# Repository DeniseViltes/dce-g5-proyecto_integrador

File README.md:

# Proyecto de diseño: Sistema de alimentación para aplicaciones industriales y automotrices
>[!TIP]
>holaa
## Grupo 5

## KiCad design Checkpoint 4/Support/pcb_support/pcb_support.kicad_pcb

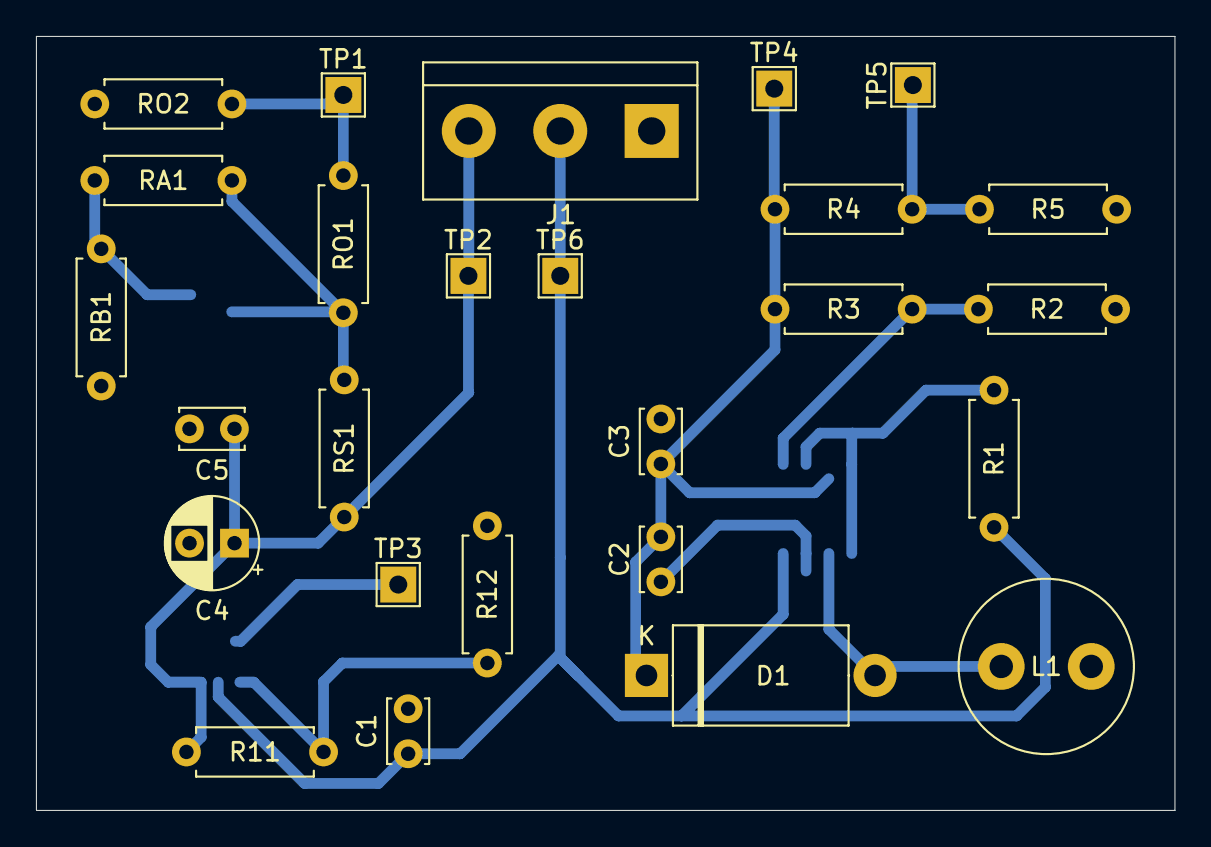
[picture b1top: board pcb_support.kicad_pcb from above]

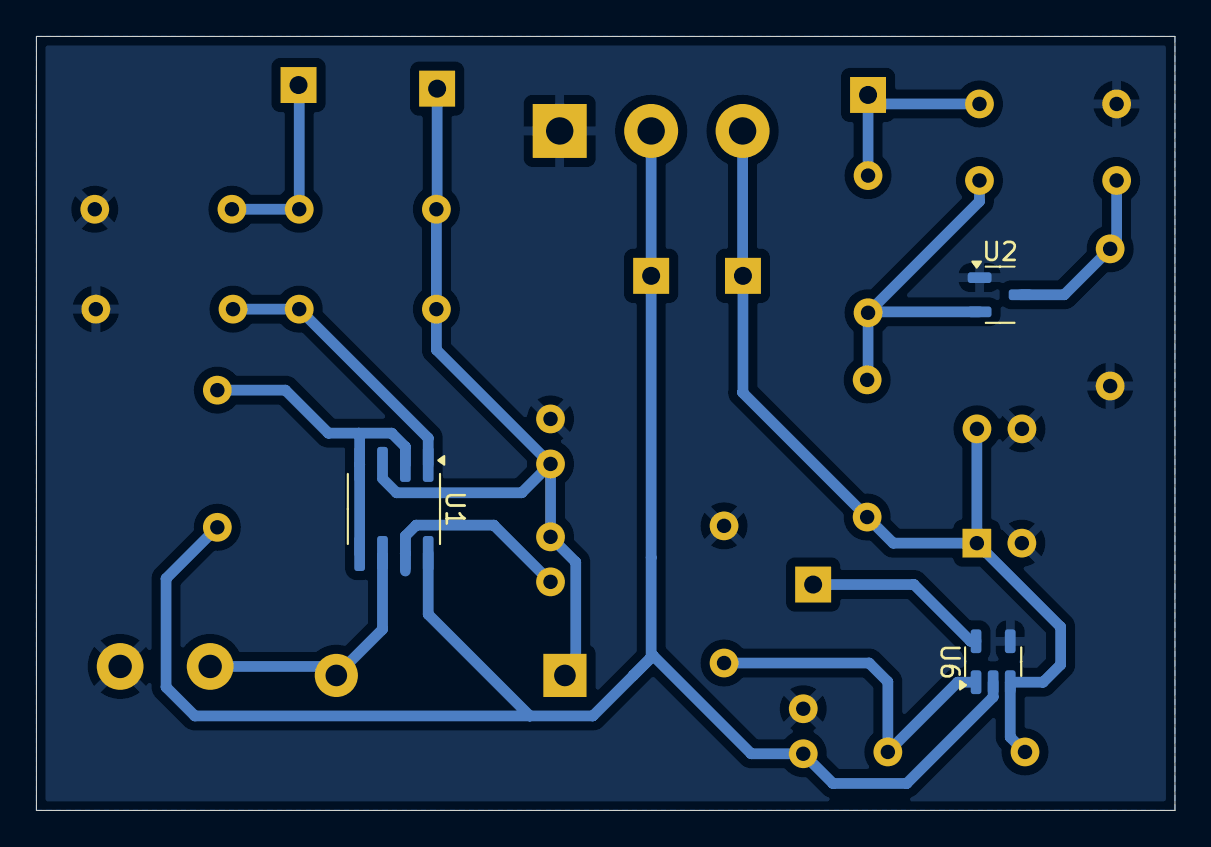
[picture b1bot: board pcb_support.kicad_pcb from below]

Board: 2 copper layers, 63.2 x 43.0 mm, 29 parts (3 on the bottom side), 14 nets.

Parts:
C1, C3: 100µ; C_Disc_D3.4mm_W2.1mm_P2.50mm
C2: 1.5n; C_Disc_D3.4mm_W2.1mm_P2.50mm
C4: 10µ; CP_Radial_D5.0mm_P2.50mm
C5: 100n; C_Disc_D3.4mm_W2.1mm_P2.50mm
D1: RBQ20T45ANZ; D_DO-27_P12.70mm_Horizontal
J1: Conn_01x03_Socket; TerminalBlock_bornier-3_P5.08mm
L1: 90µ; L_Radial_D9.5mm_P5.00mm_Fastron_07HVP
R1: 0.22; R_Axial_DIN0207_L6.3mm_D2.5mm_P7.62mm_Horizontal
R2: 8.2k; R_Axial_DIN0207_L6.3mm_D2.5mm_P7.62mm_Horizontal
R3: 953; R_Axial_DIN0207_L6.3mm_D2.5mm_P7.62mm_Horizontal
R4: 1k; R_Axial_DIN0207_L6.3mm_D2.5mm_P7.62mm_Horizontal
R5: 1.1k; R_Axial_DIN0207_L6.3mm_D2.5mm_P7.62mm_Horizontal
R11: 10k; R_Axial_DIN0207_L6.3mm_D2.5mm_P7.62mm_Horizontal
R12: 11.24k; R_Axial_DIN0207_L6.3mm_D2.5mm_P7.62mm_Horizontal
RA1: 10; R_Axial_DIN0207_L6.3mm_D2.5mm_P7.62mm_Horizontal
RB1: 100k; R_Axial_DIN0207_L6.3mm_D2.5mm_P7.62mm_Horizontal
RO1: 1.5k; R_Axial_DIN0207_L6.3mm_D2.5mm_P7.62mm_Horizontal
RO2: 1.4k; R_Axial_DIN0207_L6.3mm_D2.5mm_P7.62mm_Horizontal
RS1: 1k; R_Axial_DIN0207_L6.3mm_D2.5mm_P7.62mm_Horizontal
TP1, TP2, TP3, TP4, TP5, TP6: TestPoint; TestPoint_THTPad_2.0x2.0mm_Drill1.0mm
U1: MC33063A-Q1_TRANS; SOIC-8_3.9x4.9mm_P1.27mm
U2: TL431; SOT-23-3
U6: TLV3201; SOT-23-5

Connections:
0: C1.2, C3.2, C4.2, C5.2, J1.1, L1.2, R2.2, R5.1, R12.1, RB1.2, RO2.2, U2.1 (2), U6.4 (GND)
-VPOSA: R4.1, R5.2, TP5.1
-Vbat: C2.2, C3.1, D1.1 (+), R3.1, R4.2, TP4.1, U1.3 (GND)
unnamed: D1.2 (-), L1.1, U1.6 (SE)
unnamed: R2.1, R3.2, U1.1 (CII)
unnamed: R1.1, U1.2 (DC), U1.4 (Ipk), U1.5 (SC)
unnamed: C2.1, U1.7 (TC)
unnamed: RA1.2, RB1.1, U2.3 (1)
unnamed: RA1.1, RO1.1, RS1.2, U2.2 (3)
unnamed: R11.1, R12.2, U6.1 (IN+)
Vbat: C4.1, C5.1, J1.3, R11.2, RS1.1, TP2.1, U6.3 (Vcc)
Vbuck: C1.1, J1.2, R1.2, TP6.1, U1.8 (VCC), U6.2 (IN-)
Venable: TP3.1, U6.5 (OUT)
Vref: RO1.2, RO2.1, TP1.1

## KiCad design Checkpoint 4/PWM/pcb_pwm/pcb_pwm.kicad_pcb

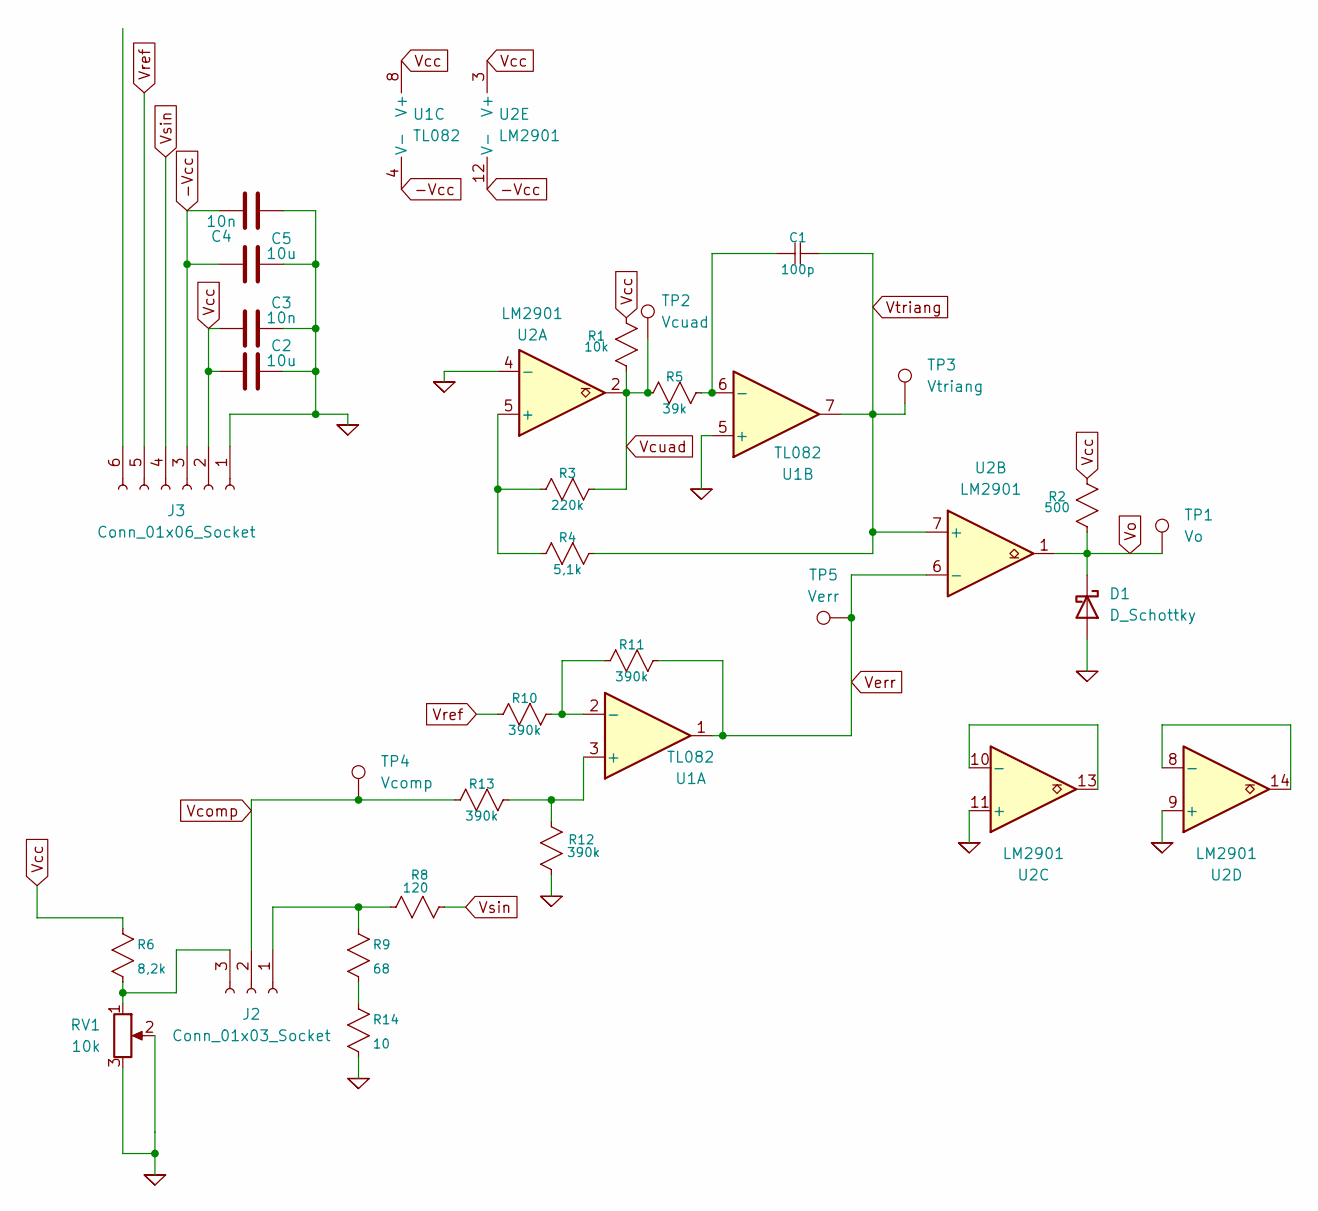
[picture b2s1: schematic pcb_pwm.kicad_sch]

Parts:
C1: 100p; C_Disc_D3.4mm_W2.1mm_P2.50mm
C2, C5: 10u; CP_Radial_D5.0mm_P2.50mm
C3, C4: 10n; C_Disc_D4.3mm_W1.9mm_P5.00mm
D1: D_Schottky; TO-220-2_Vertical
J2: Conn_01x03_Socket; PinHeader_1x03_P2.54mm_Vertical
J3: Conn_01x06_Socket; TerminalBlock_bornier-6_P5.08mm
R1: 10k; R_Axial_DIN0207_L6.3mm_D2.5mm_P7.62mm_Horizontal
R2: 500; R_Axial_DIN0207_L6.3mm_D2.5mm_P7.62mm_Horizontal
R3: 220k; R_Axial_DIN0207_L6.3mm_D2.5mm_P7.62mm_Horizontal
R4: 5,1k; R_Axial_DIN0207_L6.3mm_D2.5mm_P7.62mm_Horizontal
R5: 39k; R_Axial_DIN0207_L6.3mm_D2.5mm_P7.62mm_Horizontal
R6: 8,2k; R_Axial_DIN0207_L6.3mm_D2.5mm_P7.62mm_Horizontal
R8: 120; R_Axial_DIN0207_L6.3mm_D2.5mm_P7.62mm_Horizontal
R9: 68; R_Axial_DIN0207_L6.3mm_D2.5mm_P7.62mm_Horizontal
R10, R11, R12, R13: 390k; R_Axial_DIN0207_L6.3mm_D2.5mm_P7.62mm_Horizontal
R14: 10; R_Axial_DIN0207_L6.3mm_D2.5mm_P7.62mm_Horizontal
RV1: 10k; Potentiometer_Piher_PC-16_Single_Horizontal
TP1: Vo; TestPoint_THTPad_1.3x1.3mm_Drill0.7mm
TP2: Vcuad; TestPoint_THTPad_1.3x1.3mm_Drill0.7mm
TP3: Vtriang; TestPoint_THTPad_1.3x1.3mm_Drill0.7mm
TP4: Vcomp; TestPoint_THTPad_1.3x1.3mm_Drill0.7mm
TP5: Verr; TestPoint_THTPad_1.3x1.3mm_Drill0.7mm
U1: TL082; DIP-8_W7.62mm_Socket
U2: LM2901; DIP-14_W7.62mm_Socket

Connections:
0: C2.2, C3.2, C4.1, C5.2, D1.2 (A), J3.1, R12.2, R14.2, RV1.2, RV1.3, U1.5 (+), U2.4 (-), U2.9 (+), U2.11 (+)
-Vcc: C4.2, C5.1, J3.3, U1.4 (V-), U2.12 (V-)
unnamed: J2.1, R8.1, R9.1
unnamed: J2.3, R6.2, RV1.1
unnamed: R9.2, R14.1
unnamed: R12.1, R13.1, U1.3 (+)
unnamed: R10.1, R11.2, U1.2 (-)
unnamed: C1.2, R5.1, U1.6 (-)
unnamed: R3.2, R4.2, U2.5 (+)
unnamed: U2.10 (-), U2.13
unnamed: U2.8 (-), U2.14
Vcc: C2.1, C3.1, J3.2, R1.2, R2.2, R6.1, U1.8 (V+), U2.3 (V+)
Vcomp: J2.2, R13.2, TP4.1
Vcuad: R1.1, R3.1, R5.2, TP2.1, U2.2
Verr: R11.1, TP5.1, U1.1, U2.6 (-)
Vo: D1.1 (K), R2.1, TP1.1, U2.1
Vref: J3.5, R10.2
Vsin: J3.4, R8.2
Vtriang: C1.1, R4.1, TP3.1, U1.7, U2.7 (+)

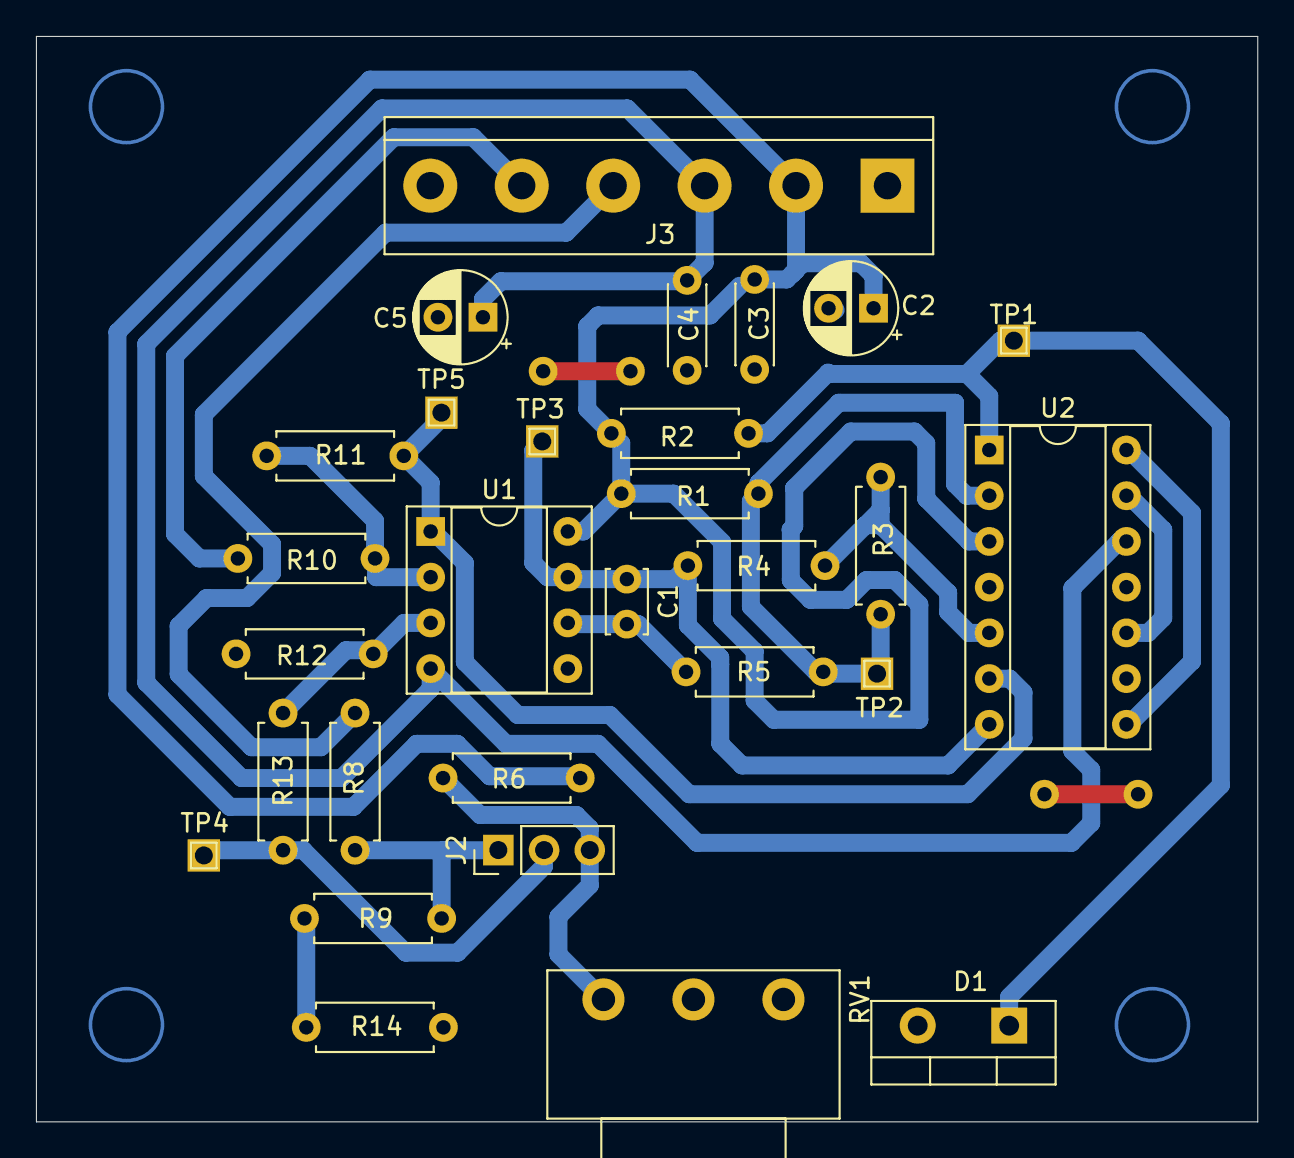
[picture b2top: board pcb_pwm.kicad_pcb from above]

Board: 2 copper layers, 67.8 x 60.3 mm, 29 parts (0 on the bottom side), 19 nets.

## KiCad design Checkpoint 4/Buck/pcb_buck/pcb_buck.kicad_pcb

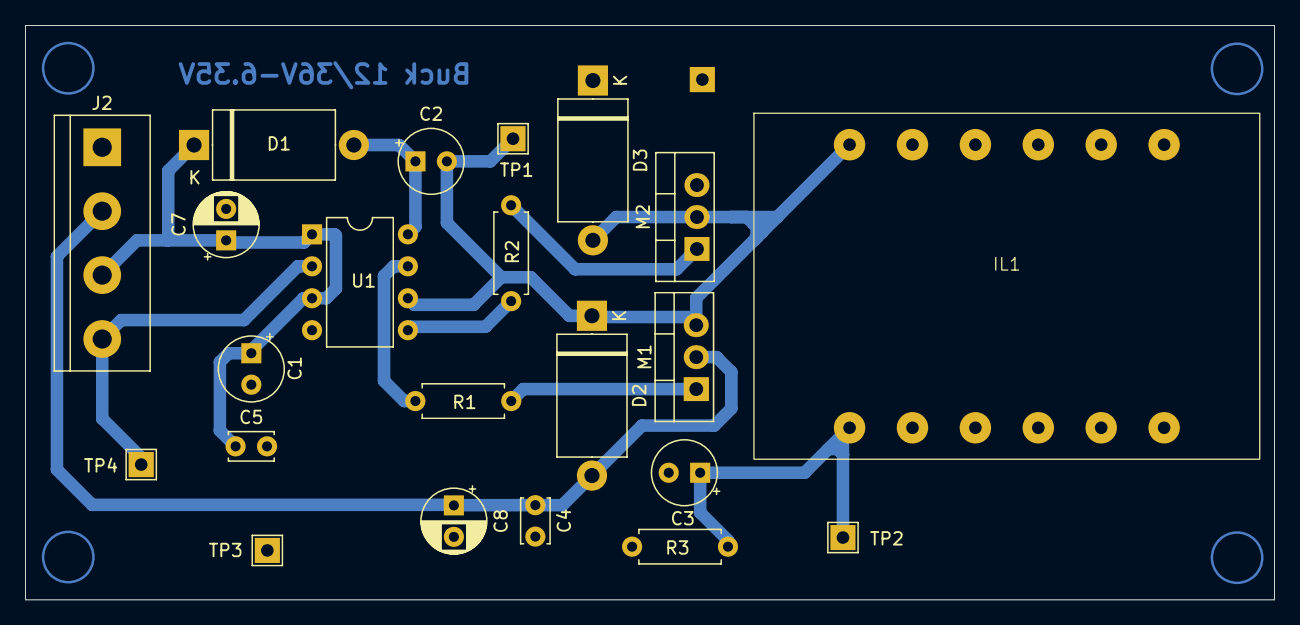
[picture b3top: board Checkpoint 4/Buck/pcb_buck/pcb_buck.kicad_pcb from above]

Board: 2 copper layers, 99.3 x 45.6 mm, 22 parts (0 on the bottom side), 11 nets.

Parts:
C1: 1µ; CP_Radial_Tantal_D5.0mm_P2.50mm
C2: 330n; CP_Radial_Tantal_D5.0mm_P2.50mm
C3: 150n; CP_Radial_Tantal_D5.0mm_P2.50mm
C4, C5: 100n; C_Disc_D3.4mm_W2.1mm_P2.50mm
C7, C8: 10u; CP_Radial_D5.0mm_P2.50mm
D1, D2, D3: D1n5822rl; D_DO-27_P12.70mm_Horizontal
IL1: 700µ; Inductor
J2: Conn_01x04_Socket; TerminalBlock_bornier-4_P5.08mm
M1, M2: IRLZ44N; TO-220-3_Vertical
R1, R2: 10; R_Axial_DIN0207_L6.3mm_D2.5mm_P7.62mm_Horizontal
R3: 390; R_Axial_DIN0207_L6.3mm_D2.5mm_P7.62mm_Horizontal
TP1: Vd; TestPoint_THTPad_2.0x2.0mm_Drill1.0mm
TP2: Vo; TestPoint_THTPad_2.0x2.0mm_Drill1.0mm
TP3: GND; TestPoint_THTPad_2.0x2.0mm_Drill1.0mm
TP4: PWM; TestPoint_THTPad_2.0x2.0mm_Drill1.0mm
U1: IR2104; DIP-8_W7.62mm

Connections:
0: C1.2, C3.2, C4.2, C5.2, C7.2, C8.2, D3.1 (+), J2.1, M2.3 (S), R3.2, TP3.1, U1.4 (COM)
unnamed: C2.1, D1.2 (-), U1.8 (LO)
unnamed: M1.1 (D), R1.1
unnamed: M2.1 (D), R2.1
unnamed: R1.2, U1.7 (VS)
unnamed: R2.2, U1.5 (VB)
Vd: C2.2, D2.1 (+), D3.2 (-), IL1.7, M1.3 (S), M2.2 (G), TP1.1, U1.6 (HO)
Vo: C3.1, IL1.1, R3.1, TP2.1
pwm: J2.4, TP4.1, U1.2 (IN)
vcc: C1.1, C5.1, C7.1, D1.1 (+), J2.3, U1.1 (VCC), U1.3 (NSD)
vdd: C4.1, C8.1, D2.2 (-), J2.2, M1.2 (G)

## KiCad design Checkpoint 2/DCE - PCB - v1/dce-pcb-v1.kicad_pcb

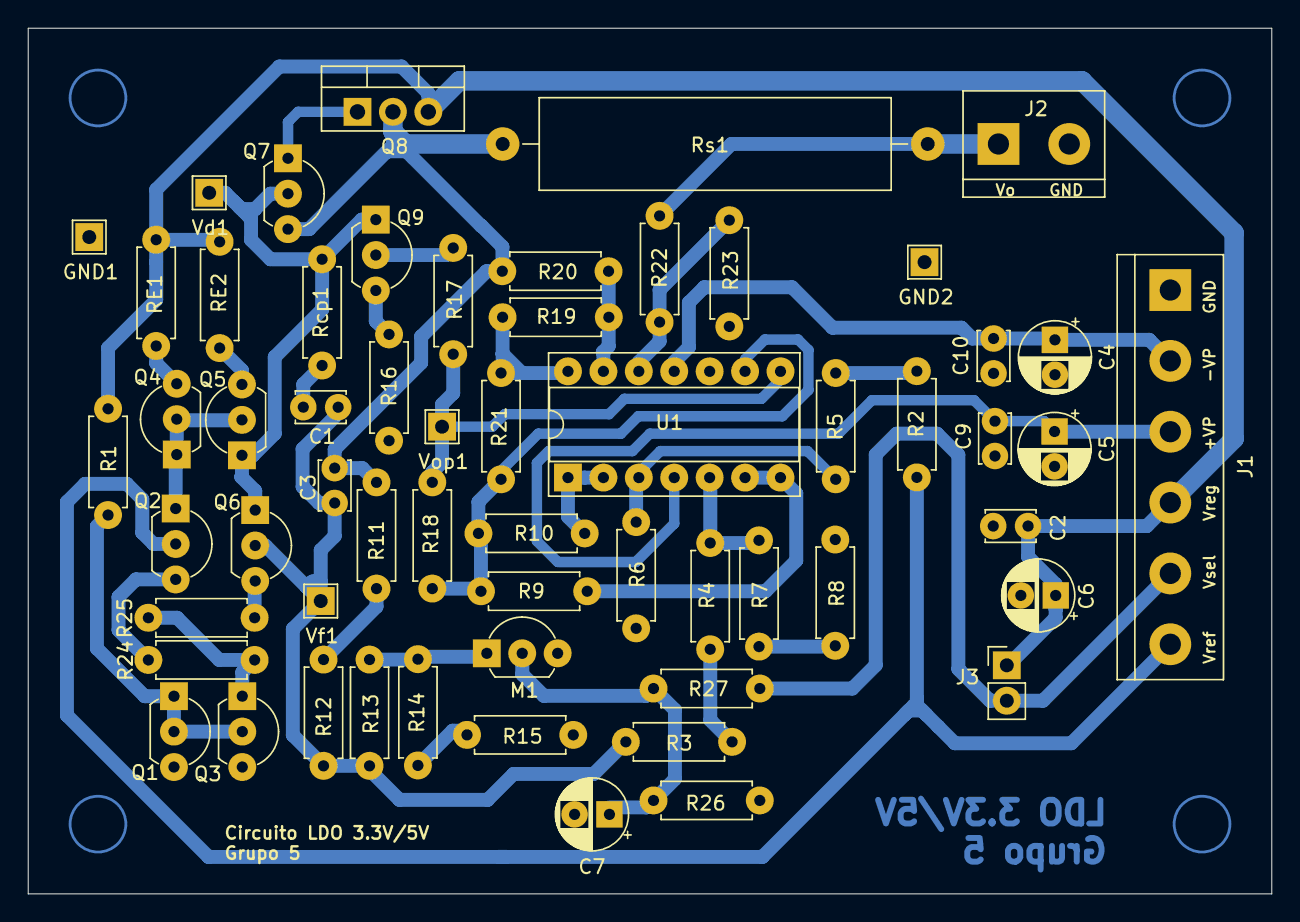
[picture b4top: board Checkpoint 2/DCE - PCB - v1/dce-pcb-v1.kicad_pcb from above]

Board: 2 copper layers, 89.2 x 62.1 mm, 59 parts (0 on the bottom side), 37 nets.

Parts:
C1: 2.2n; C_Disc_D3.4mm_W2.1mm_P2.50mm
C2, C9, C10: 10n; C_Disc_D3.4mm_W2.1mm_P2.50mm
C3: 100p; C_Disc_D3.4mm_W2.1mm_P2.50mm
C4, C5, C6: 10u; CP_Radial_D5.0mm_P2.50mm
C7: C; CP_Radial_D5.0mm_P2.50mm
GND1, GND2: TestPoint; TestPoint_THTPad_2.0x2.0mm_Drill1.0mm
J1: Conn_01x06_Socket; TerminalBlock_bornier-6_P5.08mm
J2: Conn_01x02_Socket; TerminalBlock_bornier-2_P5.08mm
J3: Conn_01x02_Socket; PinHeader_1x02_P2.54mm_Vertical
M1: 2N7000; TO-92L_Inline_Wide
Q1, Q2, Q3, Q6, Q9: BC547B; TO-92L_Inline_Wide
Q4, Q5: BC557B; TO-92L_Inline_Wide
Q7: TIP41C; TO-92L_Inline_Wide
Q8: TIP42C; TO-220-3_Vertical
R1: 3.3k; R_Axial_DIN0207_L6.3mm_D2.5mm_P7.62mm_Horizontal
R2: 5.6k; R_Axial_DIN0207_L6.3mm_D2.5mm_P7.62mm_Horizontal
R3, R7: 6.8k; R_Axial_DIN0207_L6.3mm_D2.5mm_P7.62mm_Horizontal
R4: 1.2k; R_Axial_DIN0207_L6.3mm_D2.5mm_P7.62mm_Horizontal
R5, R11: 2.7k; R_Axial_DIN0207_L6.3mm_D2.5mm_P7.62mm_Horizontal
R6, R9, R10, R21: 1.5k; R_Axial_DIN0207_L6.3mm_D2.5mm_P7.62mm_Horizontal
R8: 510; R_Axial_DIN0207_L6.3mm_D2.5mm_P7.62mm_Horizontal
R12: 390; R_Axial_DIN0207_L6.3mm_D2.5mm_P7.62mm_Horizontal
R13: 1K; R_Axial_DIN0207_L6.3mm_D2.5mm_P7.62mm_Horizontal
R14: 680; R_Axial_DIN0207_L6.3mm_D2.5mm_P7.62mm_Horizontal
R15: 270; R_Axial_DIN0207_L6.3mm_D2.5mm_P7.62mm_Horizontal
R16: 100; R_Axial_DIN0207_L6.3mm_D2.5mm_P7.62mm_Horizontal
R17, R20, R22, R26, R27: 1k; R_Axial_DIN0207_L6.3mm_D2.5mm_P7.62mm_Horizontal
R18: 100k; R_Axial_DIN0207_L6.3mm_D2.5mm_P7.62mm_Horizontal
R19, R23: 10k; R_Axial_DIN0207_L6.3mm_D2.5mm_P7.62mm_Horizontal
R24, R25: 10; R_Axial_DIN0207_L6.3mm_D2.5mm_P7.62mm_Horizontal
RE1, RE2: 470; R_Axial_DIN0207_L6.3mm_D2.5mm_P7.62mm_Horizontal
Rcp1: 220; R_Axial_DIN0207_L6.3mm_D2.5mm_P7.62mm_Horizontal
Rs1: 0.1; R_Axial_Power_L25.0mm_W6.4mm_P30.48mm
U1: LM324; DIP-14_W7.62mm_Socket
Vd1: TestPoint; TestPoint_THTPad_2.0x2.0mm_Drill1.0mm
Vf1: TestPoint; TestPoint_THTPad_2.0x2.0mm_Drill1.0mm
Vop1: TestPoint; TestPoint_THTPad_2.0x2.0mm_Drill1.0mm

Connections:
0: C2.2, C4.2, C5.2, C6.2, C7.2, C9.2, C10.2, GND1.1, GND2.1, J1.1, J2.2, M1.3 (S), Q1.3 (E), Q3.3 (E), R6.2, R8.2, R15.2, R16.2, R23.2, R26.2, U1.10 (+)
/+VPOSA: C5.1, C9.1, J1.3, U1.4 (V+)
/-VPOSA: C4.1, C10.1, J1.2, U1.11 (V-)
/Sum: R9.1, R10.1, R18.1, R21.2, U1.9 (-)
/Vf: C1.2, C3.2, Q6.2 (B), R3.2, R12.2, R13.1, Vf1.1
/Vlc: Q5.1 (C), Q6.1 (C), Q7.2 (B), Q9.1 (C), Rcp1.1, Vd1.1
/Vo: J2.1, R22.1, Rs1.1
/Vref: J1.6, Q2.2 (B), R2.2
/Vreg: C2.1, C6.1, J1.4, J3.1, Q8.3 (E), R1.1, RE1.1, RE2.1
/Vsel: J1.5, J3.2, R27.2
unnamed: C1.1, Rcp1.2
unnamed: M1.1 (D), R13.2, R14.1
unnamed: C7.1, M1.2 (G), R26.1, R27.1
unnamed: Q1.1 (C), Q1.2 (B), Q3.2 (B), R1.2
unnamed: Q2.1 (C), Q4.1 (C), Q4.2 (B), Q5.2 (B)
unnamed: Q2.3 (E), R24.1
unnamed: Q3.1 (C), R24.2, R25.1
unnamed: Q4.3 (E), RE1.2
unnamed: Q5.3 (E), RE2.2
unnamed: Q6.3 (E), R25.2
unnamed: Q7.1 (C), Q8.1 (C)
unnamed: C3.1, Q7.3 (E), Q8.2 (B), R11.1, R20.1, Rs1.2
unnamed: Q9.2 (B), R17.2
unnamed: Q9.3 (E), R16.1
unnamed: R2.1, R5.2
unnamed: R3.1, R4.2
unnamed: R7.2, R8.1
unnamed: R11.2, R12.1
unnamed: R14.2, R15.1
unnamed: R17.1, R18.2, U1.8, Vop1.1
unnamed: R19.2, R21.1, U1.14
unnamed: R5.1, R6.1, U1.3 (+)
unnamed: R10.2, U1.1, U1.2 (-)
unnamed: R4.1, R7.1, U1.5 (+)
unnamed: R9.2, U1.6 (-), U1.7
unnamed: R22.2, R23.1, U1.12 (+)
unnamed: R19.1, R20.2, U1.13 (-)

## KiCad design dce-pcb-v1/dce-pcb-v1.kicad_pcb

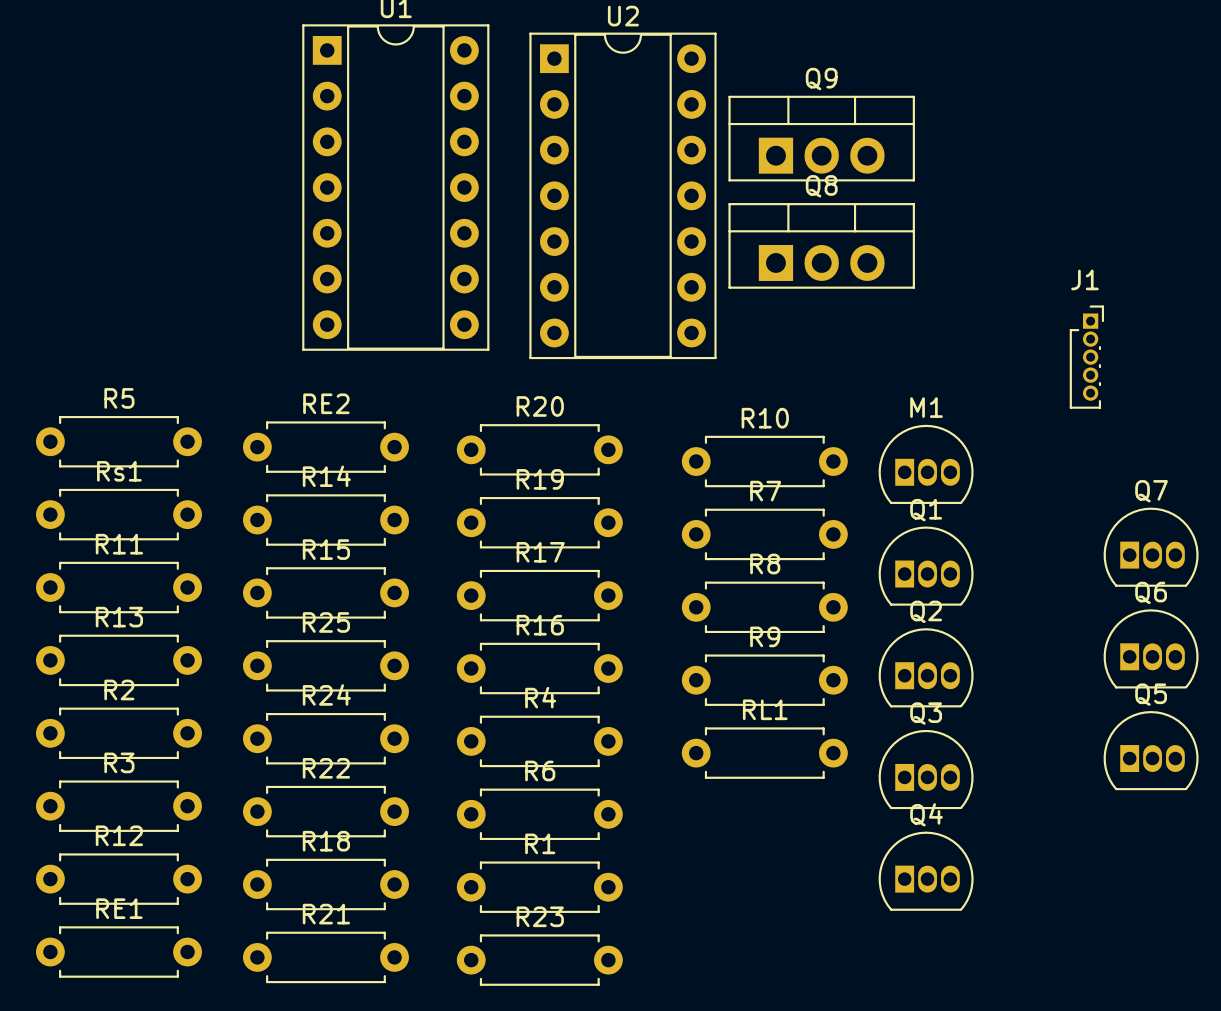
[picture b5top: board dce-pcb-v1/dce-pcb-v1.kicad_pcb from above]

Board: 2 copper layers, 42 parts (0 on the bottom side), 37 nets, no tracks yet.

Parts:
J1: Conn_01x05_Socket; PinSocket_1x05_P1.00mm_Vertical
M1: 2N7000; TO-92L_Inline
Q1, Q2: BC557B; TO-92L_Inline
Q3, Q4, Q5, Q6, Q7: BC547B; TO-92L_Inline
Q8: TIP41C; TO-220-3_Vertical
Q9: TIP42C; TO-220-3_Vertical
R1, R23: 2.7k; R_Axial_DIN0207_L6.3mm_D2.5mm_P7.62mm_Horizontal
R2: 390; R_Axial_DIN0207_L6.3mm_D2.5mm_P7.62mm_Horizontal
R3: 1K; R_Axial_DIN0207_L6.3mm_D2.5mm_P7.62mm_Horizontal
R4: 680; R_Axial_DIN0207_L6.3mm_D2.5mm_P7.62mm_Horizontal
R5: 270; R_Axial_DIN0207_L6.3mm_D2.5mm_P7.62mm_Horizontal
R6: 3.3k; R_Axial_DIN0207_L6.3mm_D2.5mm_P7.62mm_Horizontal
R7, R8, R11, R13, R15: 1k; R_Axial_DIN0207_L6.3mm_D2.5mm_P7.62mm_Horizontal
R9, R10: 10k; R_Axial_DIN0207_L6.3mm_D2.5mm_P7.62mm_Horizontal
R12, R14: 100k; R_Axial_DIN0207_L6.3mm_D2.5mm_P7.62mm_Horizontal
R16, R17, R18, R19, R22: 1.5k; R_Axial_DIN0207_L6.3mm_D2.5mm_P7.62mm_Horizontal
R20: 6.8k; R_Axial_DIN0207_L6.3mm_D2.5mm_P7.62mm_Horizontal
R21: 8.2k; R_Axial_DIN0207_L6.3mm_D2.5mm_P7.62mm_Horizontal
R24: 4.7k; R_Axial_DIN0207_L6.3mm_D2.5mm_P7.62mm_Horizontal
R25: 100; R_Axial_DIN0207_L6.3mm_D2.5mm_P7.62mm_Horizontal
RE1, RE2: 470; R_Axial_DIN0207_L6.3mm_D2.5mm_P7.62mm_Horizontal
RL1: RL; R_Axial_DIN0207_L6.3mm_D2.5mm_P7.62mm_Horizontal
Rs1: 0.1; R_Axial_DIN0207_L6.3mm_D2.5mm_P7.62mm_Horizontal
U1, U2: LM324; DIP-14_W7.62mm_Socket

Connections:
0: J1.1, M1.3 (S), Q5.3 (E), Q6.3 (E), R5.2, R9.2, R12.2, R17.2, R20.2, R22.2, R25.2, RL1.2, U1.11 (V-), U2.11 (V-)
/VPOSA: J1.2, U1.4 (V+), U2.4 (V+)
/Vf: Q4.2 (B), R2.2, R3.1, R21.2
/Vlc: Q2.1 (C), Q4.1 (C), Q7.1 (C), Q8.2 (B)
/Vo: R8.1, RL1.1, Rs1.1
/Vref: J1.3, Q3.2 (B), R24.2
/Vreg: J1.4, Q9.3 (E), R6.1, RE1.1, RE2.1
/Vsel: J1.5, M1.2 (G)
/vref-c: R13.1, R16.1, U1.8
unnamed: M1.1 (D), R3.2, R4.1
unnamed: Q1.1 (C), Q1.2 (B), Q2.2 (B), Q3.1 (C)
unnamed: Q1.3 (E), RE1.2
unnamed: Q2.3 (E), RE2.2
unnamed: Q3.3 (E), Q4.3 (E), Q6.1 (C)
unnamed: Q5.1 (C), Q5.2 (B), Q6.2 (B), R6.2
unnamed: Q7.2 (B), R15.2
unnamed: Q7.3 (E), R25.1
unnamed: Q8.1 (C), Q9.2 (B)
unnamed: Q8.3 (E), Q9.1 (C), R1.1, R7.1, Rs1.2
unnamed: R1.2, R2.1
unnamed: R4.2, R5.1
unnamed: R10.2, R11.1, U2.1
unnamed: R14.2, R15.1, U2.7
unnamed: R23.2, R24.1
unnamed: R22.1, R23.1, U1.3 (+)
unnamed: R18.2, U1.1, U1.2 (-)
unnamed: R20.1, R21.1, U1.5 (+)
unnamed: R19.2, U1.6 (-), U1.7
unnamed: R18.1, R19.1, U1.10 (+)
unnamed: R16.2, R17.1, U1.9 (-)
unnamed: U1.12 (+), U1.13 (-), U1.14
unnamed: R7.2, R9.1, U2.3 (+)
unnamed: R8.2, R10.1, U2.2 (-)
unnamed: R11.2, R12.1, U2.5 (+)
unnamed: R13.2, R14.1, U2.6 (-)
unnamed: U2.8, U2.9 (-), U2.10 (+)
unnamed: U2.12 (+), U2.13 (-), U2.14

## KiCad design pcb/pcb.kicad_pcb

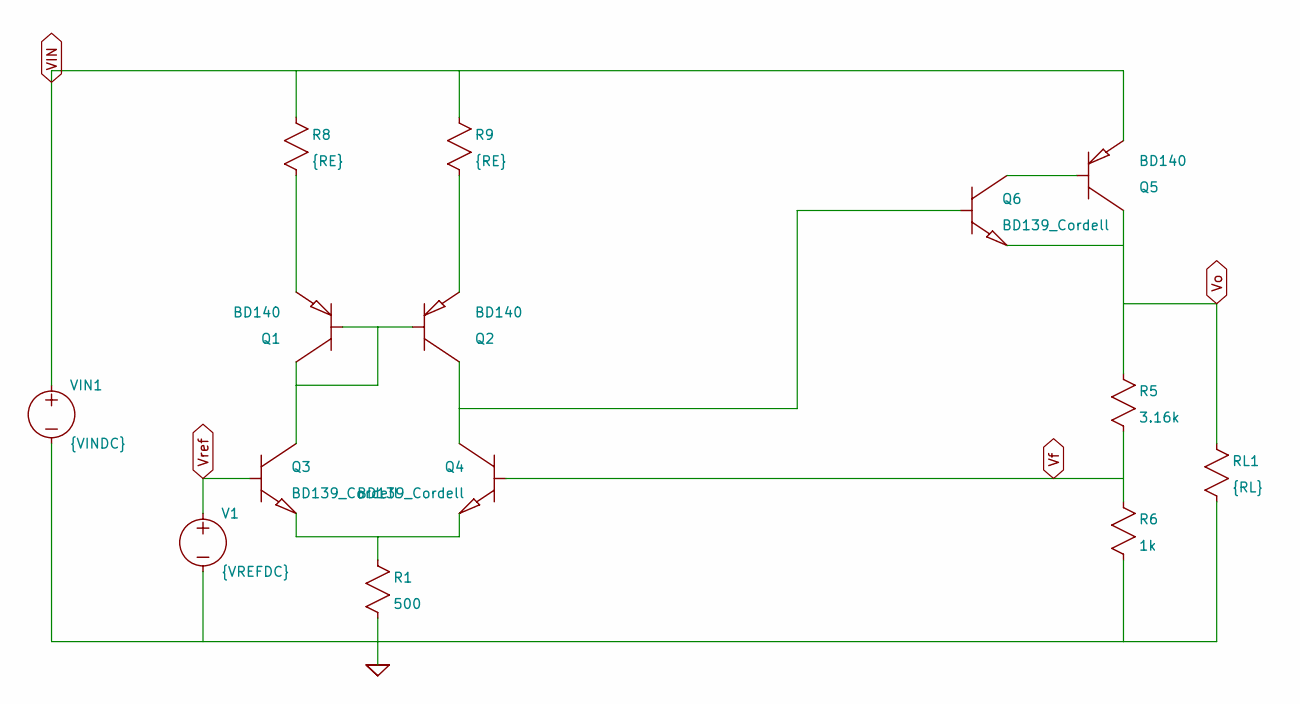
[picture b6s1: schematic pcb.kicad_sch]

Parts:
Q1, Q2, Q5: BD140; TO-126-3_Vertical
Q3, Q4, Q6: BD139_Cordell; TO-126-3_Vertical
R1: 500; R_Axial_DIN0204_L3.6mm_D1.6mm_P5.08mm_Horizontal
R5: 3.16k; R_Axial_DIN0204_L3.6mm_D1.6mm_P5.08mm_Horizontal
R6: 1k; R_Axial_DIN0204_L3.6mm_D1.6mm_P5.08mm_Horizontal
R8, R9: {RE}; R_Axial_DIN0204_L3.6mm_D1.6mm_P5.08mm_Horizontal
RL1: {RL}; R_Axial_DIN0204_L3.6mm_D1.6mm_P5.08mm_Horizontal
V1: {VREFDC}; SolderJumper-2_P1.3mm_Bridged_RoundedPad1.0x1.5mm
VIN1: {VINDC}; SolderJumper-2_P1.3mm_Bridged_RoundedPad1.0x1.5mm

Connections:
0: R1.2, R6.2, RL1.2, V1.2 (-), VIN1.2 (-)
unnamed: Q1.1 (C), Q1.2 (B), Q2.2 (B), Q3.1 (C)
unnamed: Q1.3 (E), R8.2
unnamed: Q2.1 (C), Q4.1 (C), Q6.2 (B)
unnamed: Q2.3 (E), R9.2
unnamed: Q3.3 (E), Q4.3 (E), R1.1
unnamed: Q5.2 (B), Q6.1 (C)
VIN: Q5.3 (E), R8.1, R9.1, VIN1.1 (+)
Vf: Q4.2 (B), R5.2, R6.1
Vo: Q5.1 (C), Q6.3 (E), R5.1, RL1.1
Vref: Q3.2 (B), V1.1 (+)

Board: 2 copper layers, 14 parts (0 on the bottom side), 11 nets, no tracks yet.

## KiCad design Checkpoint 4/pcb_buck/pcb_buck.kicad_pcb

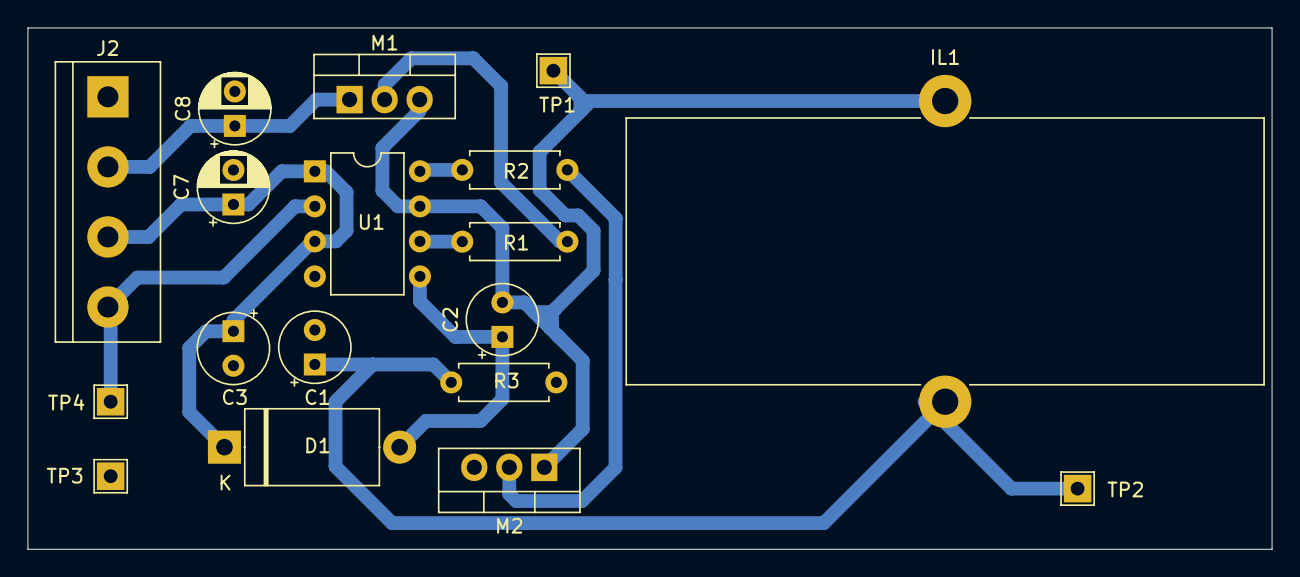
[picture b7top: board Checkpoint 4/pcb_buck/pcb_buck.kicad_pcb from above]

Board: 2 copper layers, 90.2 x 37.8 mm, 18 parts (0 on the bottom side), 11 nets.

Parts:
C1: 1µ; CP_Radial_Tantal_D5.0mm_P2.50mm
C2: 330n; CP_Radial_Tantal_D5.0mm_P2.50mm
C3: 150n; CP_Radial_Tantal_D5.0mm_P2.50mm
C7, C8: 10u; CP_Radial_D5.0mm_P2.50mm
D1: D1n5822rl; D_DO-27_P12.70mm_Horizontal
IL1: 500µ; L_Toroid_Vertical_L46.0mm_W19.1mm_P21.80mm_Bourns_5700
J2: Conn_01x04_Socket; TerminalBlock_bornier-4_P5.08mm
M1, M2: IRF530; TO-220-3_Vertical
R1, R2: 10; R_Axial_DIN0207_L6.3mm_D2.5mm_P7.62mm_Horizontal
R3: 390; R_Axial_DIN0207_L6.3mm_D2.5mm_P7.62mm_Horizontal
TP1: Vd; TestPoint_THTPad_2.0x2.0mm_Drill1.0mm
TP2: Vo; TestPoint_THTPad_2.0x2.0mm_Drill1.0mm
TP3: GND; TestPoint_THTPad_2.0x2.0mm_Drill1.0mm
TP4: PWM; TestPoint_THTPad_2.0x2.0mm_Drill1.0mm
U1: IR2104; DIP-8_W7.62mm

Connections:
0: C1.2, C3.2, C7.2, C8.2, J2.1, M2.3 (S), R3.2, TP3.1, U1.4 (COM)
unnamed: C2.1, D1.2 (-), U1.5 (VB)
unnamed: M1.2 (G), R1.1
unnamed: M2.2 (G), R2.1
unnamed: R1.2, U1.6 (HO)
unnamed: R2.2, U1.8 (LO)
Vd: C2.2, IL1.1, M1.3 (S), M2.1 (D), TP1.1, U1.7 (VS)
Vo: C3.1, IL1.2, R3.1, TP2.1
pwm: J2.4, TP4.1, U1.2 (IN)
vcc: C1.1, C7.1, D1.1 (+), J2.3, U1.1 (VCC), U1.3 (NSD)
vdd: C8.1, J2.2, M1.1 (D)

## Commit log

2024-08-30 agrega el gitignore
2024-08-30 agrega el enunciado
2024-08-31 subo el ltspice
2024-09-06 sube primer intento de simulación
2024-09-06 Sube las hojas de datos del transistor de paso
2024-09-06 nuevo esquematic
2024-09-07 agrega los cambios de la clase 9/6, ver comentarios en el archivo de spice
2024-09-07 sube últimos comentarios sobre la simulación
2024-09-07 agrega archivo de pruebas de fuente de corriente
2024-09-07 elimina archivo de simulacion viejo
2024-09-07 funciona la configuración básica
2024-09-08 Nueva versión del circuito 07/09
2024-09-08 La simulación ahora funciona bien
2024-09-09 Versión 5 de la simulación - Ahora funciona :D
2024-09-10 Clavado 750mv
2024-09-11 sube todos para poder mergear
2024-09-11 Elimino archivos extras de spice
2024-09-12 sube datashets y sube primer intento con kicad, hay que cambiar los operaciones y vincularlos con un pin, lo mismo con las fuentes
2024-09-13 Update Simulacion - v.6.asc
    separa en bloques los opamps para facilitar pasarlo a kicad
2024-09-13 sube el esquematico del pcb
2024-09-13 actualiza el pcb
2024-09-15 Version 10 de la simulacion
2024-09-20 sube informe del checkpoint 1
2024-09-20 sube solo entrega del checkpoint 1
    acomoda archivos, y elimina versiones obsoletas
2024-09-20 sube simulación de lazo de ganancia
2024-09-22 Un poco mas ordenado
2024-09-22 Simulación con 4 opamps
2024-09-23 Simulacion compensada
2024-09-24 compensado
2024-09-25 Empieza archivo de ploteo en python, y el nuevo esquemático del p
2024-09-25 sube primeros graficos en python
    arregla la corriente de foldback, pero se pasa de los 750mA
    Deja más linda la bornera del pcb
    Falta agregar test points en el pcb
2024-09-25 Simulacion final de lazos de tension y corriente
2024-09-25 Ahora si valores finales comerciales de las compensaciones de lazo
2024-09-25 Nuevos valores de R para el foldback
2024-09-25 Sube esquematico y diseño del pcb actualizados
    Falta organizar el pcb
2024-09-25 avance pcb
2024-09-26 pcb_almost_finished
2024-09-27 sube todas las simulaciones a resources
2024-09-27 Actualizacion PCB
2024-09-27 Sube curvas basicas
    foldback
    potencia
    recta de carga
    recta de linea
2024-09-27 nueva datasheet
2024-09-27 Sube transitorios del foldback
2024-09-27 valor de R de compensacion actualizado
2024-09-27 sube primer transitorio
2024-09-27 simulacion reordenada
2024-09-27 Sube lgraficos del lazo de tension sin compensar para varias RL
2024-09-27 Sube todas las simulaciones de ganancia de lazo
2024-09-28 arregla los grafiquitos de los bodes
2024-09-29 PCB actualizado
2024-09-29 valor de resistencia de compensacion corregida en el esquematico
2024-09-30 sube listita de compras
2024-10-01 pcb actualizado con recomendaciones de julio
2024-10-01 pcb_para_imprimir
2024-10-05 ojala no rompa todo
2024-10-06 nuevo pcb
2024-10-13 probando cosas en el readme
2024-10-18 sube primeros graficos de las mediciones
2024-10-28 actualiza spice con los cambios en el pcb
2024-10-30 sube carpeta cp 4
2024-10-30 sube los resultados de los componentes calculados
2024-10-31 sube cuentitas del buck sin realimentar?
    igual no queda tan bien siguiendo las cuentas del Lcr, pero supongo que es porque me falta definir cual es la Iout
2024-11-01 sigo probando valores
2024-11-01 cambio valor cap
2024-11-03 probando Valores
2024-11-06 bloque support con las librerias y datasheets
2024-11-06 PWM v1
2024-11-07 v1 buck
2024-11-07 Falta Pensar donde cambiaría con la realiment
2024-11-07 Ahi funciona el integrado, pero vo da cualquier cosa
2024-11-08 support acutalizado
2024-11-08 Sube buck
2024-11-08 sube buck con valores comerciales de R y C
2024-11-08 PWM cocinadito
2024-11-08 Revert "PWM cocinadito"
    This reverts commit b6f61ffd52ceb4e050fefbf99fd4870990937637.
2024-11-08 PWM listo, pensar donde realimentar
2024-11-08 pcb buck
2024-11-08 sube de todo
2024-11-08 pcb pwm
2024-11-08 sube ultimo intento buck
2024-11-10 ultima version
2024-11-10 update librerias support
2024-11-10 simulacion del support mas prolija
2024-11-15 sube pwm coke
2024-11-15 support mejorado
2024-11-15 pcb pwm final?
2024-11-16 cambios finales cp4
2024-11-17 Actualiza los datasheets que faltan
2024-11-17 Arregla problemas de símbolos en el buck
2024-11-17 Arregla problemas de símbolos en el pwm
2024-11-17 Arregla problemas de símbolos en el support
2024-11-18 creo que ahora si arregla el error de las librerias
2024-11-19 sube buck a lazo cerrado
2024-11-21 Buck lazo cerrado sin Diodo yet
2024-11-21 Posible diodo UF4002
2024-11-22 Comparador
2024-11-22 PCB Buck new
2024-11-23 sube cambios en el pcb del pwm, y cambios pruebas en la simu del buck
2024-11-23 agrega ultimos cambios al pcb pwm?
2024-11-23 ahora está más lindo
2024-11-23 pcb pwm y buck final
2024-11-29 Datasheets faltantes
2024-11-30 a ver si ahora si funcan los pcb sino me mato
2024-12-04 pcb support
2024-12-06 sube un monton de cosas
2024-12-06 agrega los archivos de compensacion
2024-12-06 sube pruebas de compensacion
2024-12-06 sube ultimos cambios e informe final
